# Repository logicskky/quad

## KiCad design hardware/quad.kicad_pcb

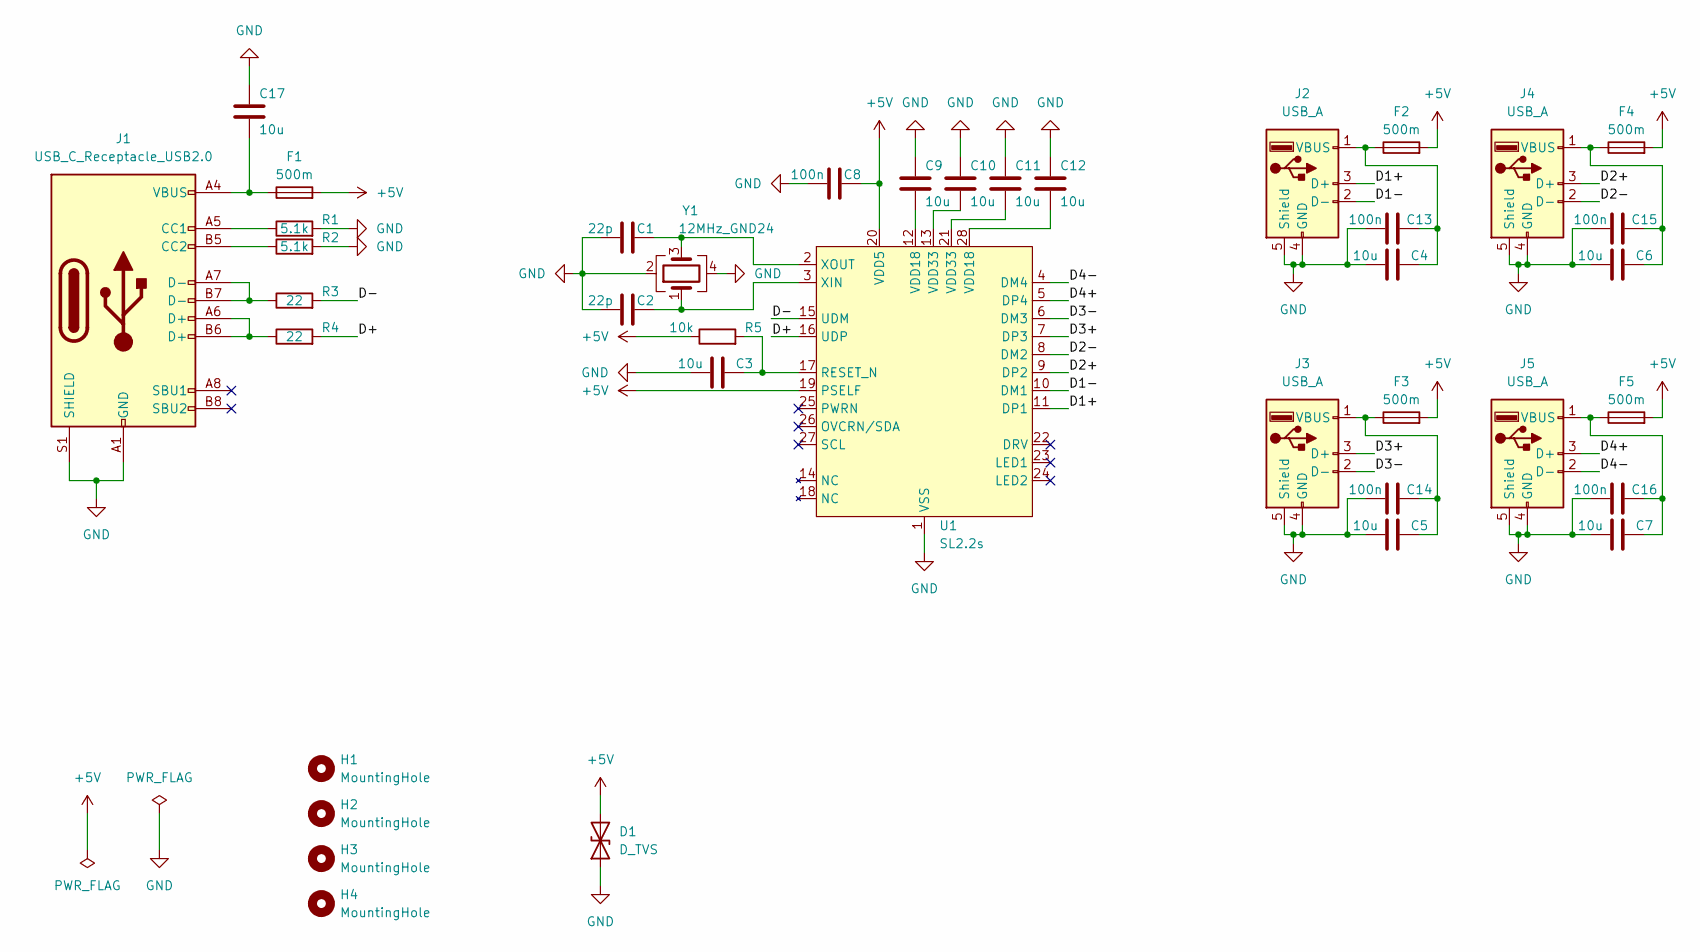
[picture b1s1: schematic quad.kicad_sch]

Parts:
C1, C2: 22p; C_0603_1608Metric
C3, C4, C5, C6, C7, C9, C10, C11, C12, C17: 10u; C_0603_1608Metric
C8, C13, C14, C15, C16: 100n; C_0603_1608Metric
D1: D_TVS; D_SMA
F1, F2, F3, F4, F5: 500m; Fuse_0603_1608Metric
H1, H2, H3, H4: MountingHole; MountingHole_2.2mm_M2_Pad
J1: USB_C_Receptacle_USB2.0; USB_C_Receptacle_HRO_TYPE-C-31-M-12
J2, J3, J4, J5: USB_A; USB_A_Side
R1, R2: 5.1k; R_0603_1608Metric
R3, R4: 22; R_0603_1608Metric
R5: 10k; R_0603_1608Metric
U1: SL2.2s; SSOP-28_3.9x9.9mm_P0.635mm
Y1: 12MHz_GND24; Crystal_SMD_3225-4Pin_3.2x2.5mm

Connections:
+5V: C8.2, D1.2 (A2), F1.2, F2.2, F3.2, F4.2, F5.2, R5.1, U1.19 (PSELF), U1.20 (VDD5)
/D1+: J2.3 (D+), U1.11 (DP1)
/D1-: J2.2 (D-), U1.10 (DM1)
/D2+: J4.3 (D+), U1.9 (DP2)
/D2-: J4.2 (D-), U1.8 (DM2)
/D3+: J3.3 (D+), U1.7 (DP3)
/D3-: J3.2 (D-), U1.6 (DM3)
/D4+: J5.3 (D+), U1.5 (DP4)
/D4-: J5.2 (D-), U1.4 (DM4)
/D+: R4.2, U1.16 (UDP)
/D-: R3.2, U1.15 (UDM)
GND: C1.1, C2.1, C3.1, C4.1, C5.1, C6.1, C7.1, C8.1, C9.1, C10.1, C11.1, C12.1, C13.1, C14.1, C15.1, C16.1, C17.1, D1.1 (A1), J1.A1 (GND), J1.A12 (GND), J1.B1 (GND), J1.B12 (GND), J1.S1 (SHIELD), J2.4 (GND), J2.5 (Shield), J3.4 (GND), J3.5 (Shield), J4.4 (GND), J4.5 (Shield), J5.4 (GND), J5.5 (Shield), R1.2, R2.2, U1.1 (VSS), Y1.2, Y1.4
unnamed: C1.2, U1.2 (XOUT), Y1.3
unnamed: C2.2, U1.3 (XIN), Y1.1
unnamed: C3.2, R5.2, U1.17 (RESET_N)
unnamed: C9.2, U1.12 (VDD18)
unnamed: C10.2, U1.13 (VDD33)
unnamed: C11.2, U1.21 (VDD33)
unnamed: C12.2, U1.28 (VDD18)
unnamed: C4.2, C13.2, F2.1, J2.1 (VBUS)
unnamed: C5.2, C14.2, F3.1, J3.1 (VBUS)
unnamed: C6.2, C15.2, F4.1, J4.1 (VBUS)
unnamed: C7.2, C16.2, F5.1, J5.1 (VBUS)
unnamed: C17.2, F1.1, J1.A4 (VBUS), J1.A9 (VBUS), J1.B4 (VBUS), J1.B9 (VBUS)
unnamed: J1.A5 (CC1), R1.1
unnamed: J1.A6 (D+), J1.B6 (D+), R4.1
unnamed: J1.A7 (D-), J1.B7 (D-), R3.1
unnamed: J1.B5 (CC2), R2.1

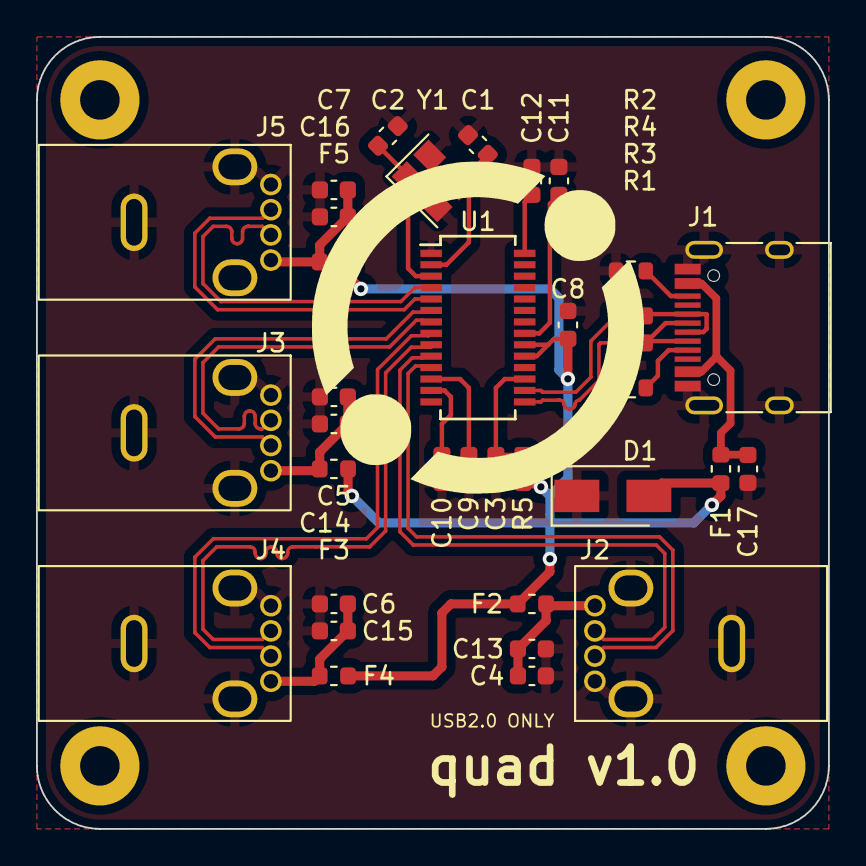
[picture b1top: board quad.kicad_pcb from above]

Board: 2 copper layers, 44.0 x 44.0 mm, 39 parts (0 on the bottom side), 28 nets.

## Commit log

2023-09-16 Adjust directory structure and complete the schematic
2023-09-16 Add a footprint of a special kind of USB-A receptacle
2023-09-28 Add a symbol for SL2.2s and place all symbols and footprints in lib directory
2023-09-28 Change the IC from FE1.1s to SL2.2s, and release the schematic v1.0_alpha
2023-09-29 Update the footprint USB_A_Side
2023-09-29 Release the PCB v1.0_alpha
2023-09-29 Adjust directory structure
